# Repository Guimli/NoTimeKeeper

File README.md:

# NoTimeKeeper

During one of our evenings at the Arcade Club, a Konami Silent Scope cabinet displayed the dreaded error message: 11P!
This error is known to indicate that the TimeKeeper, a NVRAM used to store the cabinet's settings and scores is running low on battery power and needs replacing.
The M48T58Y, which is the name of this NVRAM in Konami cabinet of this generation, has two functions: non-volatile RAM and internal clock. And the battery life is given as 10 years. So this component has to be replaced every 10 years.
25 years after the creation of this terminal, I thought that there was probably a better component to replace this expensive perishable component. So I naturally turned my attention to F-RAM. F-RAM is non-volatile RAM, but does not require a battery. And it has a data retention time of 120 years. Much longer than NAND or NOR memory. We still have to manage the internal clock. But while browsing the forums, I've found that the only games that really need the clock are Battle Tryst and Police 911.. Last but not least, the M48T58Y has two ChipEnable pins. One is active high and the other is active low. Although SilentScope doesn't use the ChipEnable in its high state, as I couldn't check that it was the same on all Konami terminals of this generation, and to facilitate compatibility in my universal programmer, I added a bit of combinatorial logic to recreate the missing ChipEnable on the F-RAM.
After conventional reprogramming of the first 16 bits so that the terminal recognises this new TimeKeeper, the game went from 11P error to Backup Memory Error. You then press the test button on the terminal and set the various essential parameters (calibration of the rifle in my case on SilentScope).
The result is perfect. The game now behaves exactly as if the TimeKeeper were an original M48T58Y. But I don't have to worry about replacing this component again in my lifetime.

Approximate cost for one NoTimeKeeper (costs can reduced if you build several modules) :

- FM16W08-SG : 7 €
- 74LVC2G00DP : 0.50 €
- Capacitor 100nF 0805 : 0.15 €
- PCB (with Shipping cost) : 23 €

Total : 30.65€

I can sell you this module for the same price if you don't want to assemble it yourself. Contact me on guimli@free.fr

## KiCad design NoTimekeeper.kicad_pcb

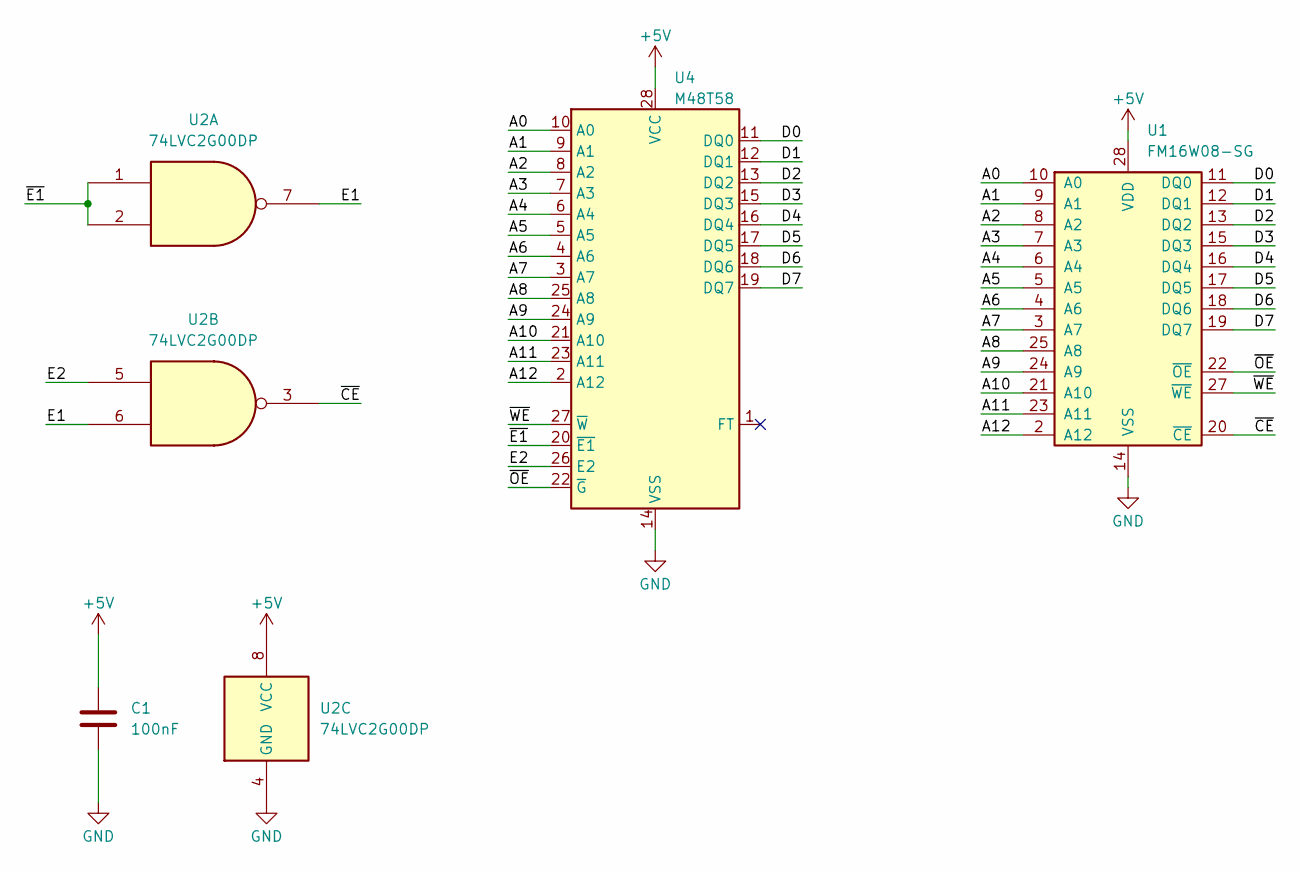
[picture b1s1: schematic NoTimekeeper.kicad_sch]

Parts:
C1: 100nF; C_0805_2012Metric
U1: FM16W08-SG; SOIC-28W_7.5x17.9mm_P1.27mm
U2: 74LVC2G00DP; TSSOP-8_3x3mm_P0.65mm
U4: M48T58; DIP-28_W15.24mm_Socket

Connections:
+5V: C1.1, U1.28 (VDD), U2.8 (VCC), U4.28 (VCC)
/A0: U1.10 (A0), U4.10 (A0)
/A1: U1.9 (A1), U4.9 (A1)
/A2: U1.8 (A2), U4.8 (A2)
/A3: U1.7 (A3), U4.7 (A3)
/A4: U1.6 (A4), U4.6 (A4)
/A5: U1.5 (A5), U4.5 (A5)
/A6: U1.4 (A6), U4.4 (A6)
/A7: U1.3 (A7), U4.3 (A7)
/A8: U1.25 (A8), U4.25 (A8)
/A9: U1.24 (A9), U4.24 (A9)
/A10: U1.21 (A10), U4.21 (A10)
/A11: U1.23 (A11), U4.23 (A11)
/A12: U1.2 (A12), U4.2 (A12)
/D0: U1.11 (DQ0), U4.11 (DQ0)
/D1: U1.12 (DQ1), U4.12 (DQ1)
/D2: U1.13 (DQ2), U4.13 (DQ2)
/D3: U1.15 (DQ3), U4.15 (DQ3)
/D4: U1.16 (DQ4), U4.16 (DQ4)
/D5: U1.17 (DQ5), U4.17 (DQ5)
/D6: U1.18 (DQ6), U4.18 (DQ6)
/D7: U1.19 (DQ7), U4.19 (DQ7)
/E1: U2.6, U2.7
/E2: U2.5, U4.26 (E2)
/~CE: U1.20 (~CE), U2.3
/~E1: U2.1, U2.2, U4.20 (~E1)
/~OE: U1.22 (~OE), U4.22 (~G)
/~WE: U1.27 (~WE), U4.27 (~W)
GND: C1.2, U1.14 (VSS), U2.4 (GND), U4.14 (VSS)

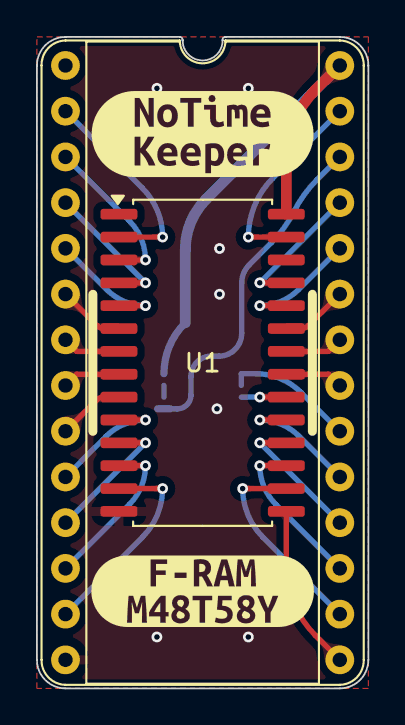
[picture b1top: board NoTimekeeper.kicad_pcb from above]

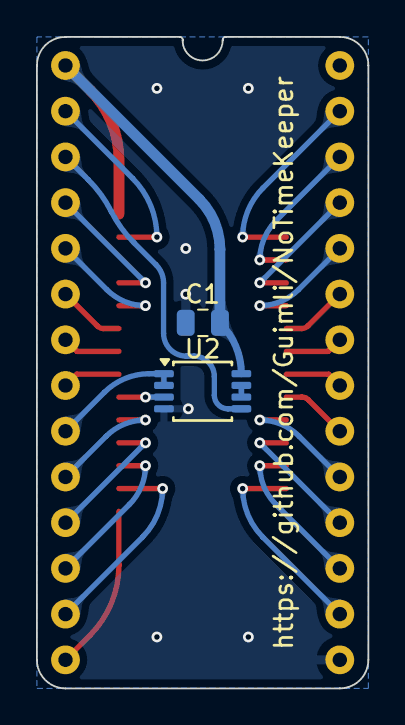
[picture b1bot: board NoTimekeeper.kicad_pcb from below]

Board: 2 copper layers, 18.4 x 36.2 mm, 6 parts (2 on the bottom side), 29 nets.

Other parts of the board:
kibuzzard-679CF58C: G***; kibuzzard-679CF58C
kibuzzard-679CF65F: G***; kibuzzard-679CF65F

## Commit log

2025-06-02 Update README.md
    Police 911 also needs the clock
